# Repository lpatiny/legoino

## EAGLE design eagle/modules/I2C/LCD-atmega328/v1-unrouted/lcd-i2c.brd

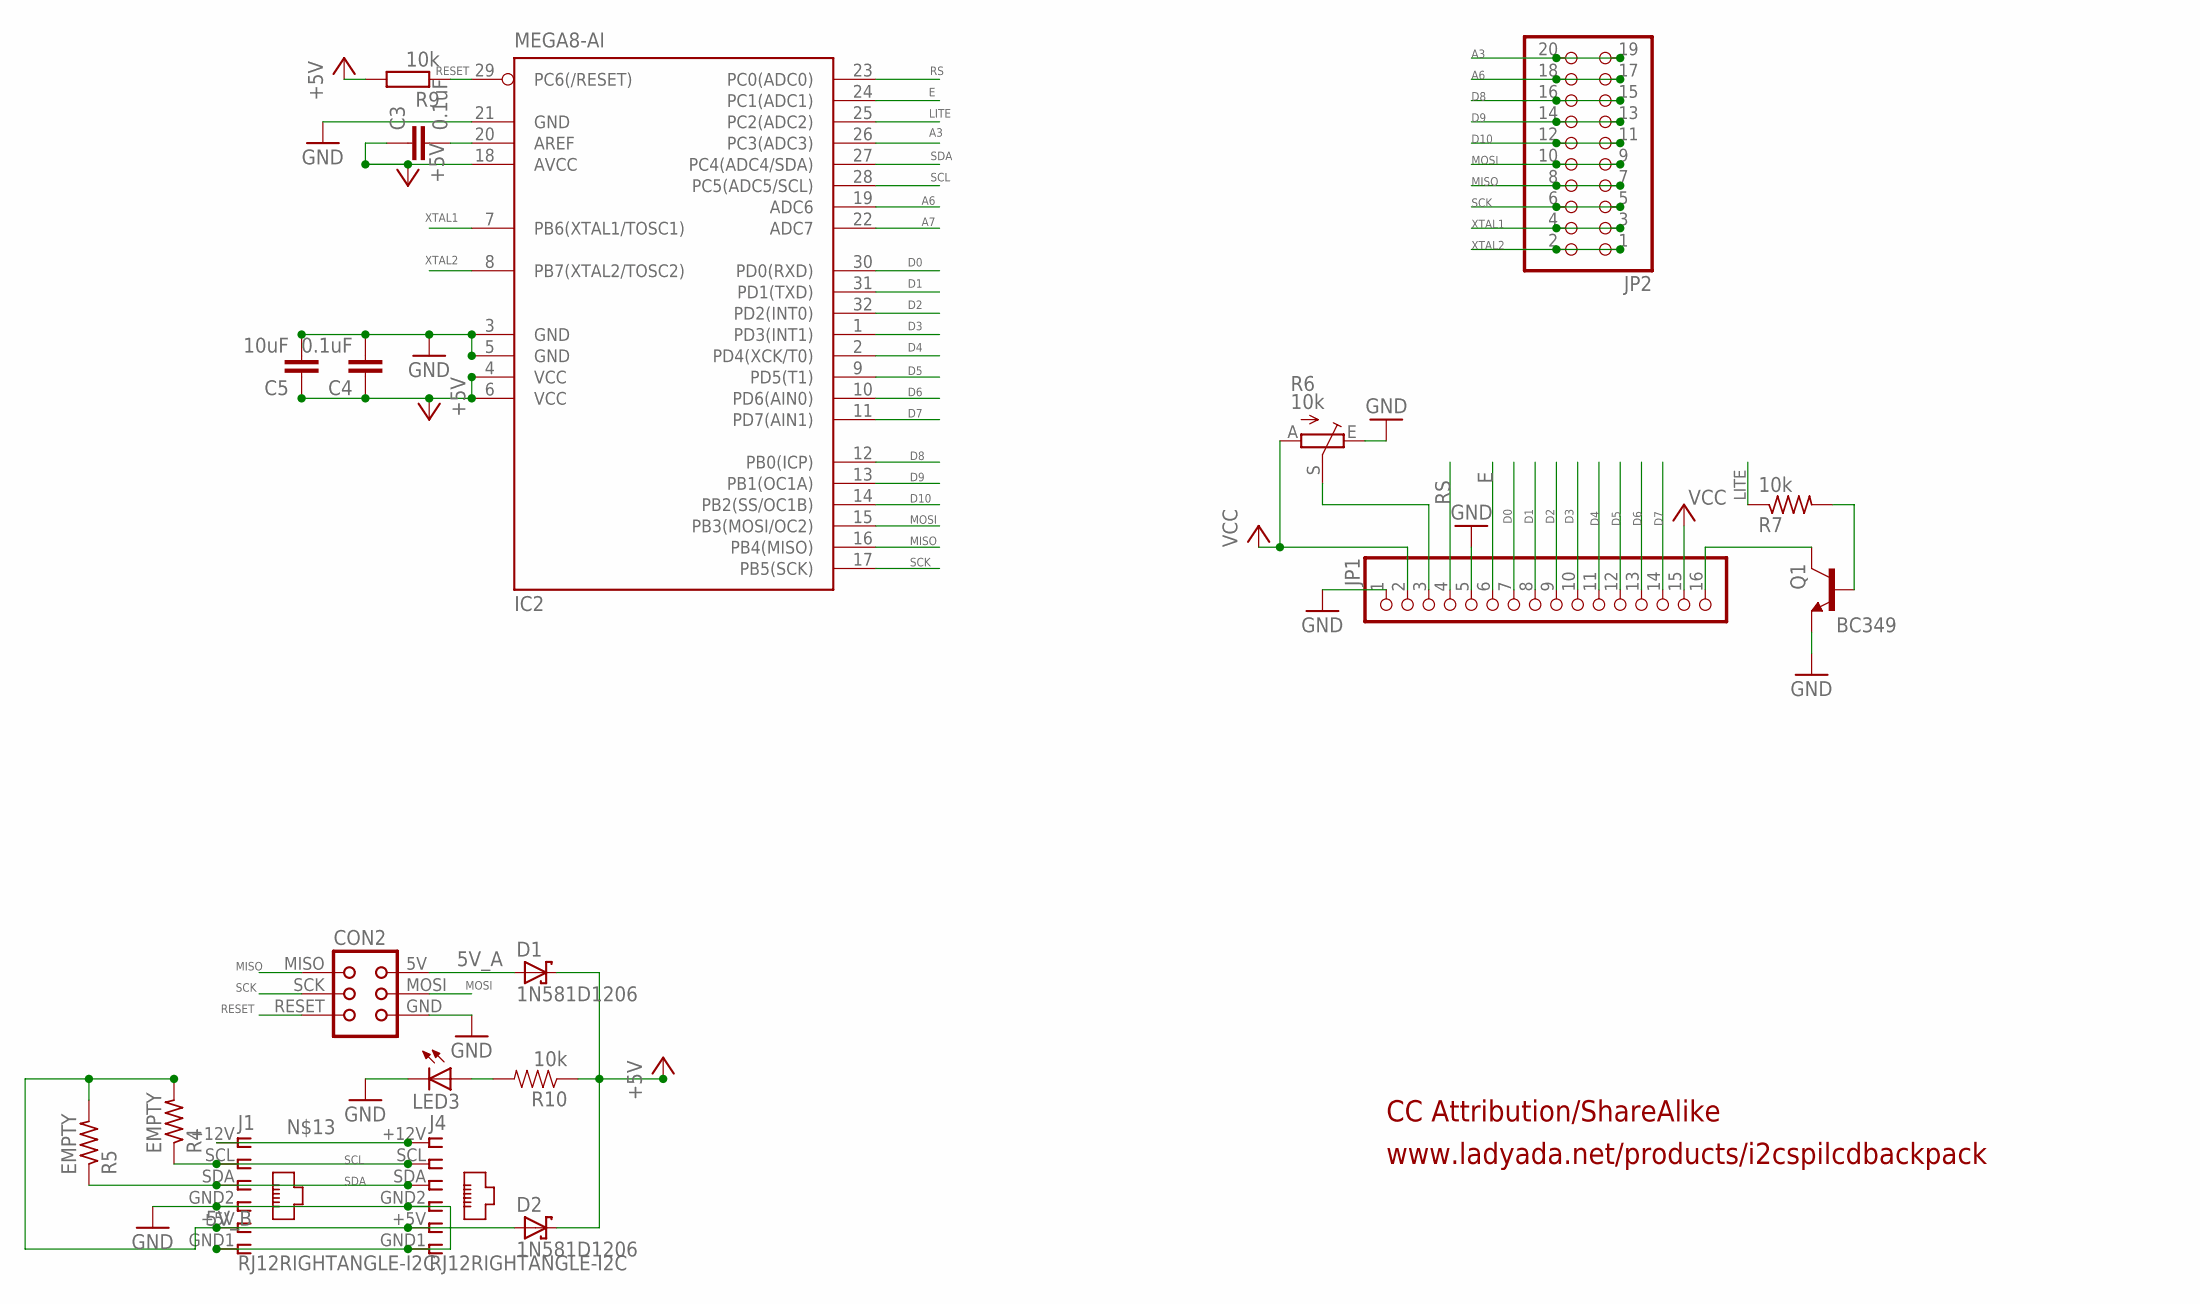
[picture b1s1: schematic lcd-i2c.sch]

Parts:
C3, C4: 0.1uF; C1206
C5: 10uF; C1206
CON2: TINYISPTAG; TC2030-MCP
D1, D2: 1N581D1206; LED-1206
IC2: MEGA8-AI; TQFP32-08
J1, J4: RJ12RIGHTANGLE-I2C; RJ12-RIGHTANGLE-I2C
JP1: PINHD-1X16; 1X16
JP2: PINHD-2X10; 2X10
LED3: LEDCHIP-LED0603; CHIP-LED0603
Q1: BC349; TO92-EBC
R4, R5: EMPTY; M1206
R6: 10k; CA6V
R7, R9: 10k; M1206
R10: 10k; 0603-RES

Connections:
5V_A: CON2.5V (VCC), D1.A
5V_B: D2.A, J1.+5V (5), J4.+5V (5), R4.2, R5.2
+5V: C3.1, C4.1, C5.1, D1.C, D2.C, IC2.4 (VCC), IC2.6 (VCC), IC2.18 (AVCC), R9.2, R10.1
A3: IC2.26 (PC3(ADC3)), JP2.19, JP2.20
A6: IC2.19 (ADC6), JP2.17, JP2.18
A7: IC2.22 (ADC7)
D0: IC2.30 (PD0(RXD)), JP1.7
D1: IC2.31 (PD1(TXD)), JP1.8
D2: IC2.32 (PD2(INT0)), JP1.9
D3: IC2.1 (PD3(INT1)), JP1.10
D4: IC2.2 (PD4(XCK/T0)), JP1.11
D5: IC2.9 (PD5(T1)), JP1.12
D6: IC2.10 (PD6(AIN0)), JP1.13
D7: IC2.11 (PD7(AIN1)), JP1.14
D8: IC2.12 (PB0(ICP)), JP2.15, JP2.16
D9: IC2.13 (PB1(OC1A)), JP2.13, JP2.14
D10: IC2.14 (PB2(SS/OC1B)), JP2.11, JP2.12
E: IC2.24 (PC1(ADC1)), JP1.6
GND: C4.2, C5.2, CON2.GND, IC2.3 (GND), IC2.5 (GND), IC2.21 (GND), J1.GND1 (6), J1.GND2 (4), J4.GND1 (6), J4.GND2 (4), JP1.1, JP1.5, LED3.C, Q1.E, R6.E
LITE: IC2.25 (PC2(ADC2)), R7.1
MISO: CON2.MISO, IC2.16 (PB4(MISO)), JP2.7, JP2.8
MOSI: CON2.MOSI, IC2.15 (PB3(MOSI/OC2)), JP2.9, JP2.10
unnamed: C3.2, IC2.20 (AREF)
unnamed: JP1.16, Q1.C
unnamed: Q1.B, R7.2
unnamed: JP1.3, R6.S
unnamed: J1.+12V (1), J4.+12V (1)
unnamed: LED3.A, R10.2
RESET: CON2.RESET, IC2.29 (PC6(/RESET)), R9.1
RS: IC2.23 (PC0(ADC0)), JP1.4
SCK: CON2.SCK, IC2.17 (PB5(SCK)), JP2.5, JP2.6
SCL: IC2.28 (PC5(ADC5/SCL)), J1.SCL (2), J4.SCL (2), R4.1
SDA: IC2.27 (PC4(ADC4/SDA)), J1.SDA (3), J4.SDA (3), R5.1
VCC: JP1.2, JP1.15, R6.A
XTAL1: IC2.7 (PB6(XTAL1/TOSC1)), JP2.3, JP2.4
XTAL2: IC2.8 (PB7(XTAL2/TOSC2)), JP2.1, JP2.2

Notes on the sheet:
www.ladyada.net/products/i2cspilcdbackpack
CC Attribution/ShareAlike

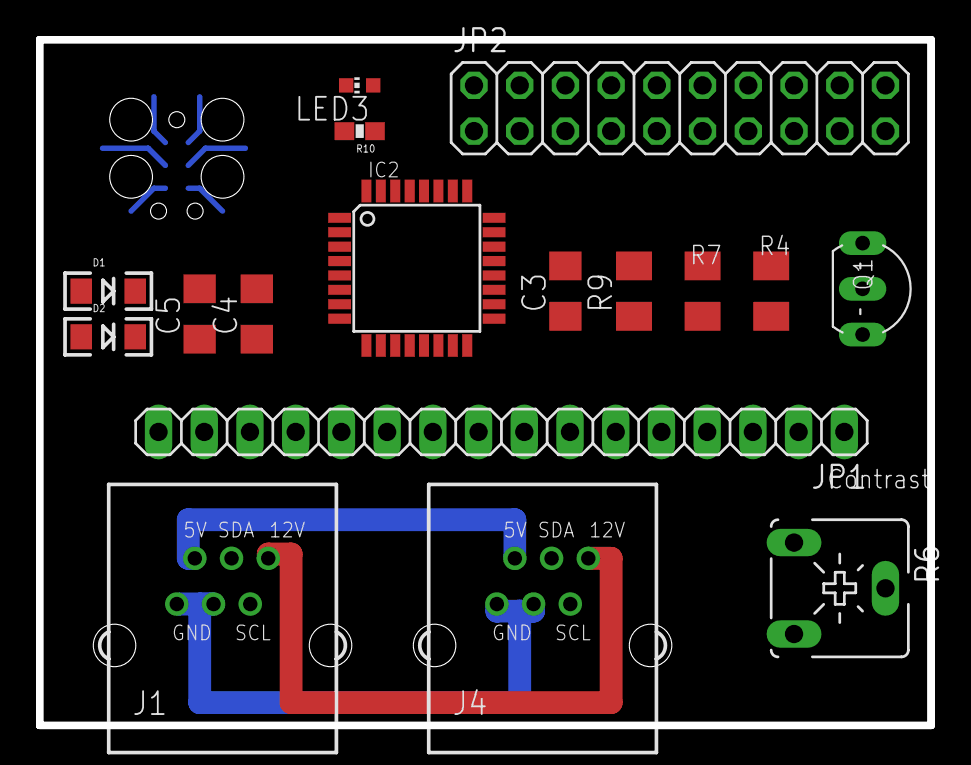
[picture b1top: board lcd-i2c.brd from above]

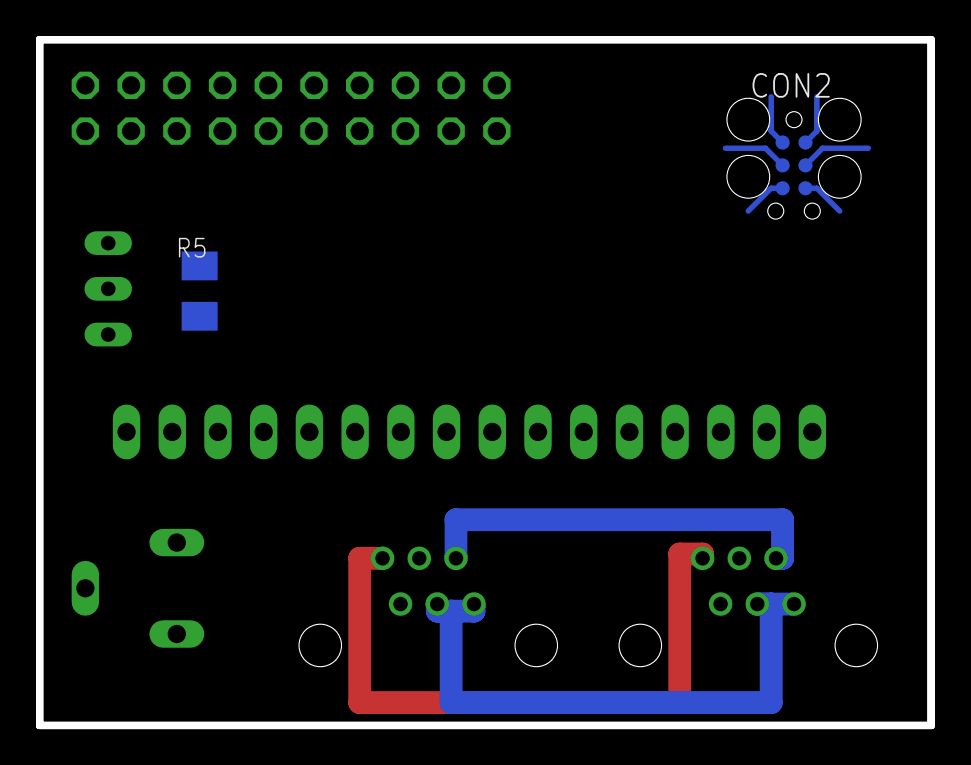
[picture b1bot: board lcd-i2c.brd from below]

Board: 2 copper layers, 49.5 x 38.1 mm, 19 parts (2 on the bottom side), 35 nets.

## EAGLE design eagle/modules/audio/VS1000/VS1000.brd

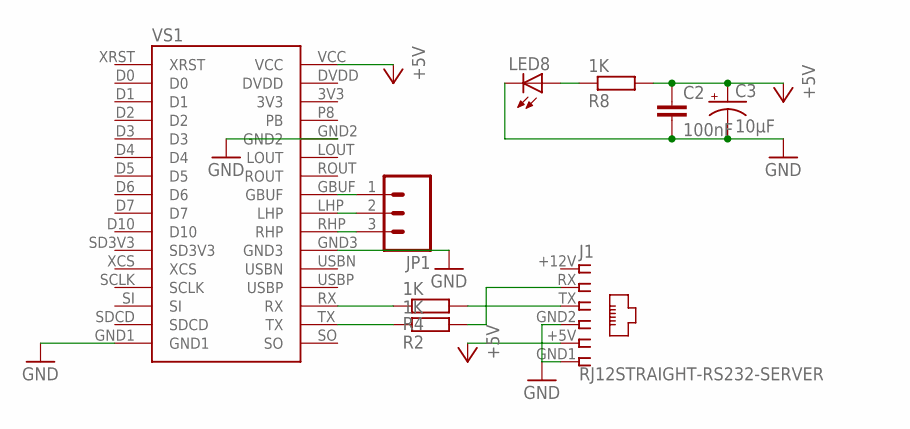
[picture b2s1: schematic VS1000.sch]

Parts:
C2: 100nF; C1206
C3: 10µF; EIA3216
J1: RJ12STRAIGHT-RS232-SERVER; RJ12-STRAIGHT-RS232
JP1: M03LONGPADS; 1X03_LONGPADS
LED8: LED3MM
R2, R4, R8: 1K; M1206
VS1: VS1000

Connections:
1: J1.+12V (1)
+5V: C2.1, C3.A (+), J1.+5V (5), R8.2, VS1.VCC
GND: C2.2, C3.C (-), J1.GND1 (6), J1.GND2 (4), LED8.K (C), VS1.GND1, VS1.GND2, VS1.GND3
unnamed: R4.1, VS1.RX
unnamed: JP1.1, VS1.GBUF
unnamed: R2.1, VS1.TX
unnamed: JP1.2, VS1.LHP
unnamed: JP1.3, VS1.RHP
unnamed: J1.RX (2), R2.2
unnamed: J1.TX (3), R4.2
unnamed: LED8.A, R8.1
SCLK: VS1.SCLK
SD3V3: VS1.SD3V3
SI: VS1.SI
XCS: VS1.XCS

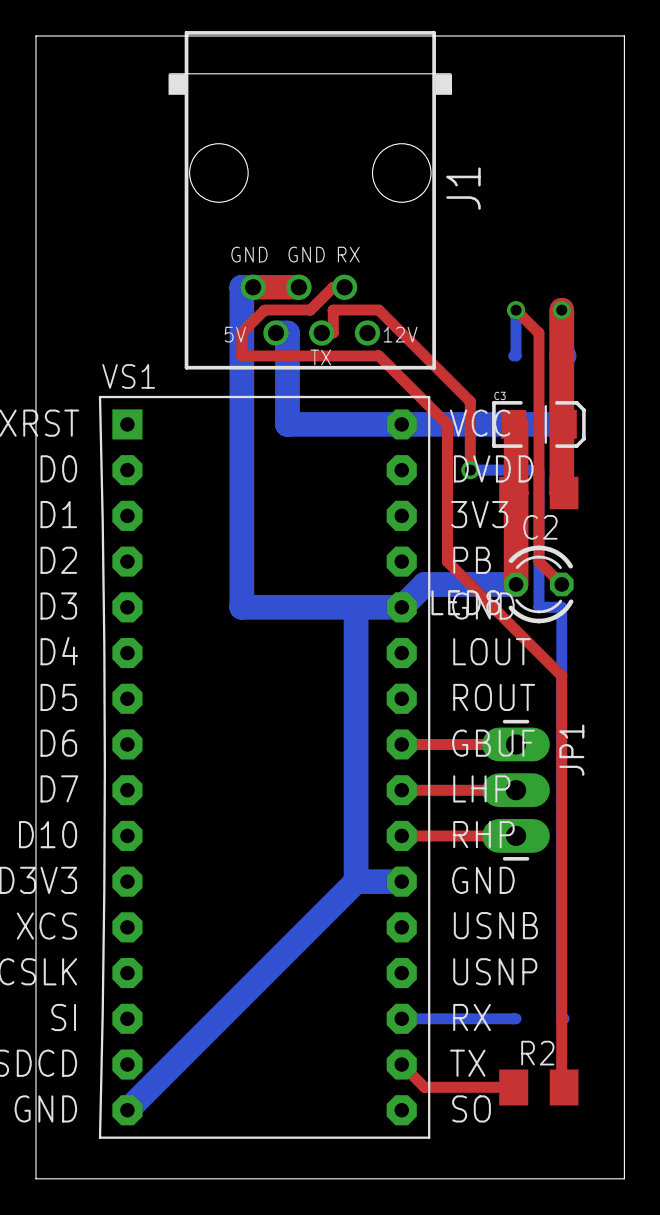
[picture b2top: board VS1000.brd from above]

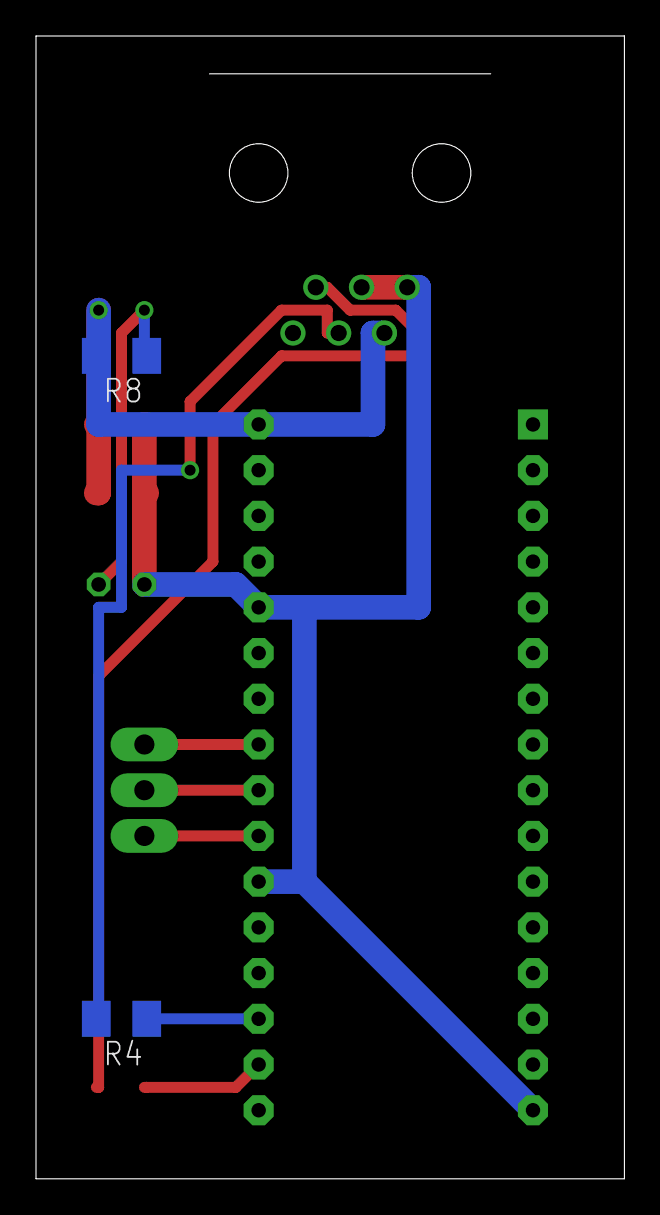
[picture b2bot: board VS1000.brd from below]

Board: 2 copper layers, 32.7 x 63.5 mm, 9 parts (2 on the bottom side), 10 nets.

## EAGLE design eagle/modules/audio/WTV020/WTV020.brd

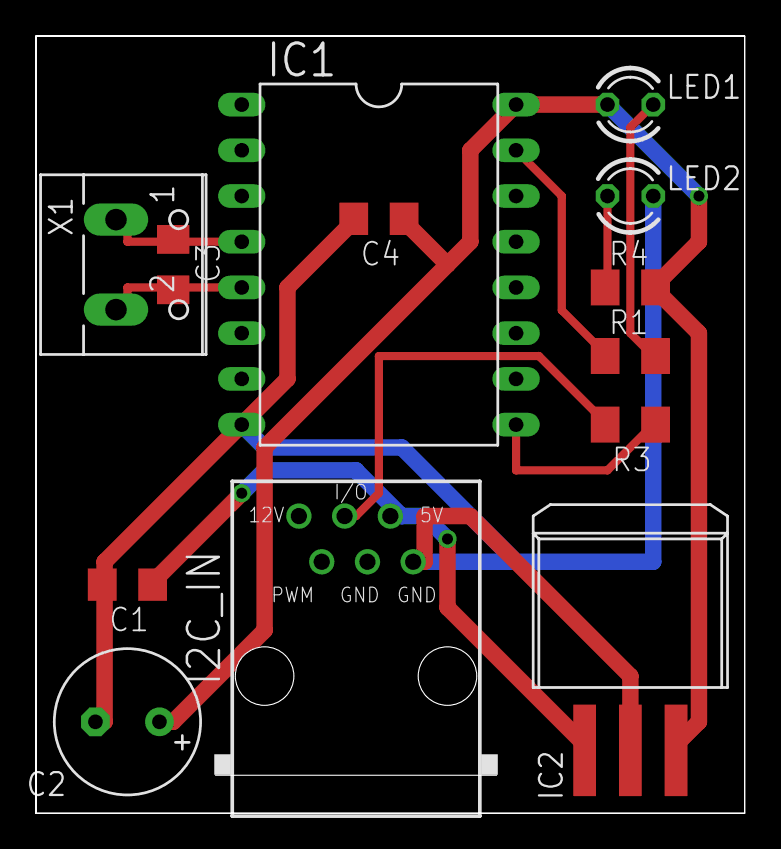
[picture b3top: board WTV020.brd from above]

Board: 2 copper layers, 39.4 x 43.2 mm, 13 parts (0 on the bottom side), 10 nets.

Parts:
C1: 470nF; C1206
C2: 33uF 10V; E3,5-8
C3, C4: 100nF; C1206
I2C_IN: I2C 1; RJ12-STRAIGHT
IC1: DIL16-6
IC2: LM3940IS-3.3F; DD-3
LED1, LED2: LED3MM
R1, R3, R4: 1K; M1206
X1: W237-102

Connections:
+3V3: C2.+, C4.1, IC1.16, IC2.3, LED1.A, R4.2
+5V: C1.1, I2C_IN.+5V, IC2.1
GND: C1.2, C2.-, C4.2, I2C_IN.GND1, IC1.8, IC2.2, LED2.K
unnamed: IC1.9, R3.1
unnamed: LED1.K, R1.2
unnamed: IC1.15, R1.1
unnamed: C3.1, IC1.4, X1.1
unnamed: C3.2, IC1.5, X1.2
unnamed: LED2.A, R4.1
SDA: I2C_IN.I/O, R3.2

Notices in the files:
parts and their libraries:
lpatiny: ©2009 ROFA.cz - modified and updated by Robert Darlington ‹rdarlington@gmail.com›
SparkFun: Licensing: CC v3.0 Share-Alike You are welcome to use this library for commercial purposes.
